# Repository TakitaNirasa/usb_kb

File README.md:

# Двухкнопочная клавиатура

[Проект печатной платы](https://github.com/TakitaNirasa/usb_kb/tree/main/sch_pcb)

[3D модели](https://github.com/TakitaNirasa/usb_kb/tree/main/3d_models%26drawings)

[Код](https://github.com/TakitaNirasa/usb_kb/tree/main/code/usb_kb_103)

[Схема](https://github.com/TakitaNirasa/usb_kb/tree/main/sch_pcb/usb_kb.pdf)

Для сборки проекта:
1. Перейти в директорию code/usb_kb_103/Debug
2. Собрать проект командой make all (Для сборки требуются пакеты: make, stlink-tools, binutils-arm-none-eabi)
3. Подключить плату к программатору (см. схему) и запитать её по usb кабелю
4. Ввести команду ./load_stm32

Скрин 3d модели корпуса для красоты:

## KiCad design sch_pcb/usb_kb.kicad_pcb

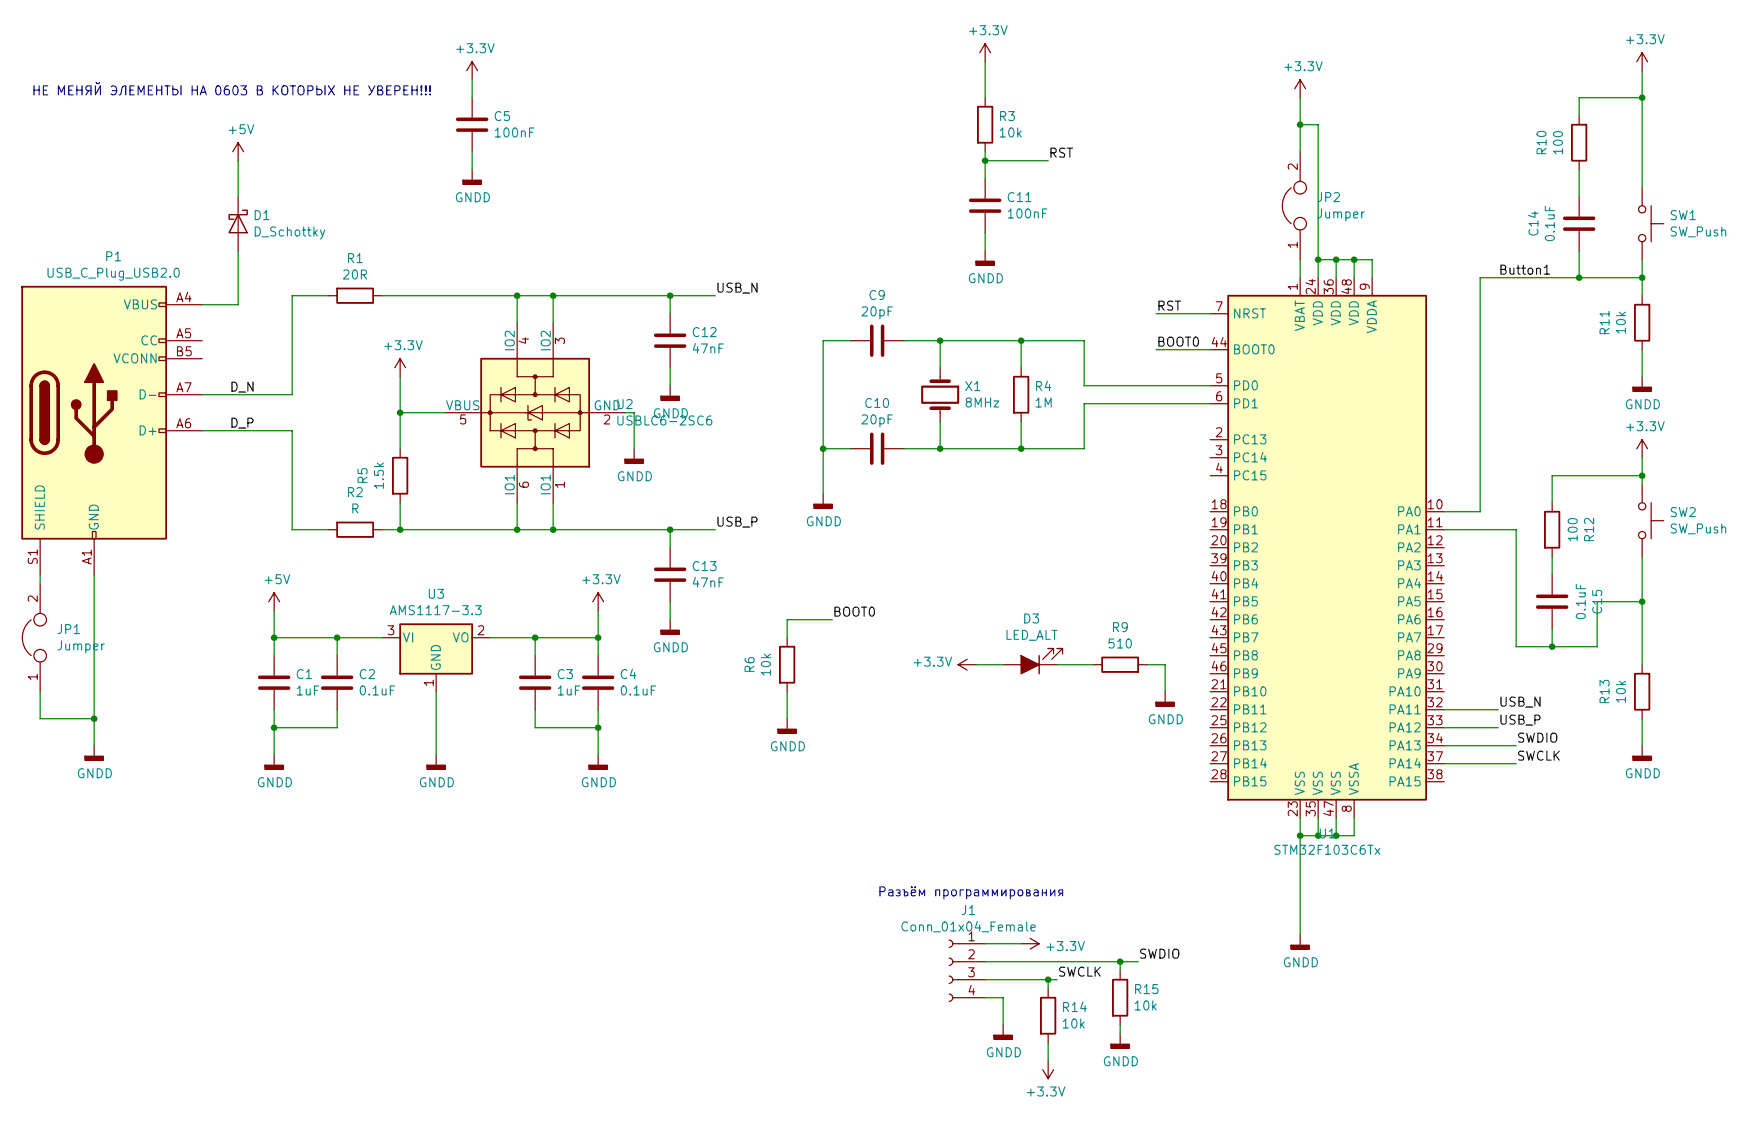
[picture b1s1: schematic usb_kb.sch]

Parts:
C1, C3: 1uF; C_0603_1608Metric_Pad1.05x0.95mm_HandSolder
C2, C4, C14, C15: 0.1uF; C_0603_1608Metric_Pad1.05x0.95mm_HandSolder
C5, C11: 100nF; C_0603_1608Metric_Pad1.05x0.95mm_HandSolder
C9, C10: 20pF; C_0603_1608Metric_Pad1.05x0.95mm_HandSolder
C12, C13: 47nF; C_0603_1608Metric_Pad1.05x0.95mm_HandSolder
D1: D_Schottky; D_MiniMELF_Handsoldering
D3: LED_ALT; D_0805_2012Metric_Pad1.15x1.40mm_HandSolder
J1: Conn_01x04_Female; PinHeader_1x04_P2.54mm_Vertical
JP1, JP2: Jumper; SolderJumper-2_P1.3mm_Open_TrianglePad1.0x1.5mm
P1: USB_C_Plug_USB2.0; USB_C_Receptacle_HRO_TYPE-C-31-M-12
R1: 20R; R_0603_1608Metric_Pad1.05x0.95mm_HandSolder
R2: R; R_0603_1608Metric_Pad1.05x0.95mm_HandSolder
R3, R6, R11, R13, R14, R15: 10k; R_0603_1608Metric_Pad1.05x0.95mm_HandSolder
R4: 1M; R_0603_1608Metric_Pad1.05x0.95mm_HandSolder
R5: 1.5k; R_0603_1608Metric_Pad1.05x0.95mm_HandSolder
R9: 510; R_0603_1608Metric_Pad1.05x0.95mm_HandSolder
R10, R12: 100; R_0603_1608Metric_Pad1.05x0.95mm_HandSolder
SW1, SW2: SW_Push; SW_Cherry_MX_1.00u_PCB
U1: STM32F103C6Tx; LQFP-48_7x7mm_P0.5mm
U2: USBLC6-2SC6; SOT-23-6
U3: AMS1117-3.3; SOT-223-3_TabPin2
X1: 8MHz; Crystal_HC49-4H_Vertical

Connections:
+3V3: C3.1, C4.1, C5.1, D3.2 (A), J1.1, JP2.2, R3.1, R5.1, R10.2, R12.1, R14.2, SW1.1, SW2.1, U1.9 (VDDA), U1.24 (VDD), U1.36 (VDD), U1.48 (VDD), U2.5 (VBUS), U3.2 (VO)
+5V: C1.1, C2.1, D1.1 (K), U3.3 (VI)
/BOOT0: R6.1, U1.44 (BOOT0)
/Button1: C14.2, R11.2, SW1.2, U1.10 (PA0)
/D_N: P1.A7 (D-), R1.2
/D_P: P1.A6 (D+), R2.2
/RST: C11.1, R3.2, U1.7 (NRST)
/SWCLK: J1.3, R14.1, U1.37 (PA14)
/SWDIO: J1.2, R15.1, U1.34 (PA13)
/USB_N: C12.1, R1.1, U1.32 (PA11), U2.3 (IO2), U2.4 (IO2)
/USB_P: C13.1, R2.1, R5.2, U1.33 (PA12), U2.1 (IO1), U2.6 (IO1)
GNDD: C1.2, C2.2, C3.2, C4.2, C5.2, C9.2, C10.2, C11.2, C12.2, C13.2, J1.4, JP1.1, P1.A1 (GND), P1.A12 (GND), P1.B1 (GND), P1.B12 (GND), R6.2, R9.2, R11.1, R13.1, R15.2, U1.8 (VSSA), U1.23 (VSS), U1.35 (VSS), U1.47 (VSS), U2.2 (GND), U3.1 (GND)
unnamed: C9.1, R4.1, U1.5 (PD0), X1.1
unnamed: C10.1, R4.2, U1.6 (PD1), X1.2
unnamed: C14.1, R10.1
unnamed: C15.1, R13.2, SW2.2, U1.11 (PA1)
unnamed: C15.2, R12.2
unnamed: D1.2 (A), P1.A4 (VBUS), P1.A9 (VBUS), P1.B4 (VBUS), P1.B9 (VBUS)
unnamed: D3.1 (K), R9.1
unnamed: JP1.2, P1.S1 (SHIELD)
unnamed: JP2.1, U1.1 (VBAT)

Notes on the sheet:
НЕ МЕНЯЙ ЭЛЕМЕНТЫ НА 0603 В КОТОРЫХ НЕ УВЕРЕН!!!
Разъём программирования

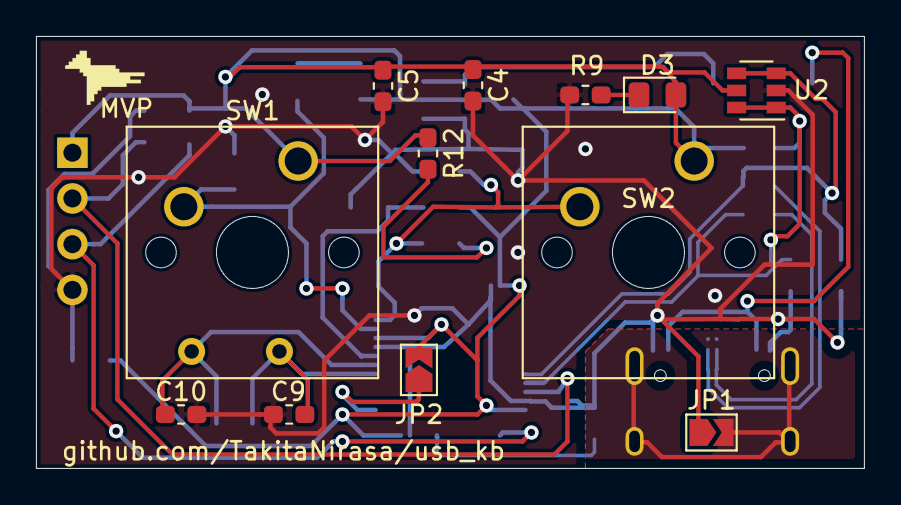
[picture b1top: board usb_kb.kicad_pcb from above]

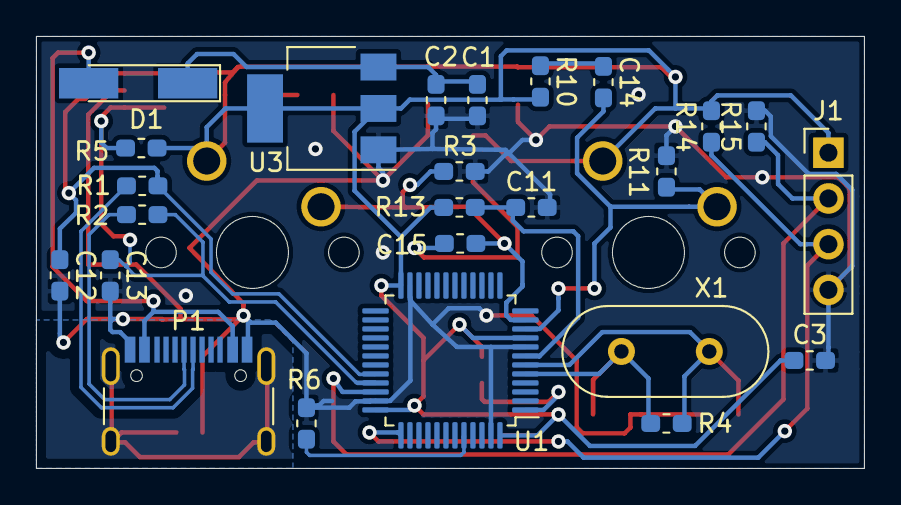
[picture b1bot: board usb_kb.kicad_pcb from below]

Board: 2 copper layers, 46.0 x 24.0 mm, 37 parts (25 on the bottom side), 21 nets.

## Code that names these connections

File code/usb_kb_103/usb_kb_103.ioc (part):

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Mcu.Name=STM32F103C(4-6)Tx
Mcu.Package=LQFP48
Mcu.UserName=STM32F103C6Tx
PA0-WKUP.Mode=SYS_WakeUp0
PA0-WKUP.Signal=SYS_WKUP
PA1.Signal=GPIO_Input
PA11.Mode=Device
PA11.Signal=USB_DM
PA12.Mode=Device
PA12.Signal=USB_DP
PA13.Mode=Serial_Wire
PA13.Signal=SYS_JTMS-SWDIO
PA14.Mode=Serial_Wire
PA14.Signal=SYS_JTCK-SWCLK
PA3.Signal=GPIO_Input
PD0-OSC_IN.Mode=HSE-External-Oscillator
PD0-OSC_IN.Signal=RCC_OSC_IN
PD1-OSC_OUT.Mode=HSE-External-Oscillator
PD1-OSC_OUT.Signal=RCC_OSC_OUT
RCC.HSEDivPLL=RCC_HSE_PREDIV_DIV2
RCC.HSE_VALUE=16000000
RCC.SYSCLKFreq_VALUE=72000000
RCC.SYSCLKSource=RCC_SYSCLKSOURCE_PLLCLK
board=custom

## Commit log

2021-09-28 Added sources
2021-09-28 Scetches added
2021-09-28 Readme.md update
2021-09-28 Added first half of f405 pisos prj
2021-09-28 Second part of f405 commit
2021-09-28 Added links
2021-09-28 Добавлен тупой комментарий для примера коммита
2021-09-28 Андрей изменил схему, добавил стабилизатор
2021-09-28 Update main.c
    Показываю Андрею как коммитить
2021-09-29 добавлена кнопка на PA0 которая делает копипаст
2021-09-29 Андрей добавил питание, Никита доделал
2021-09-29 Добавлена кнопа и мелкие правки
    Добавлена кнопа и мелкие правки
2021-09-30 ошибка R11. Конечный вариант
2021-10-01 Новые посадочные места
2021-10-01 Исправил посадочное место USB
2021-10-05 Разработал схему
2021-10-11 Переделал схему, добавил дифф пару
2021-10-11 Добавил герберы
2021-10-12 Поправил герберы
2023-07-26 Добавлен код для целевого контроллера
2023-07-26 Добавлена схема
2023-07-26 Добавлена ссылка на схему в ридми
